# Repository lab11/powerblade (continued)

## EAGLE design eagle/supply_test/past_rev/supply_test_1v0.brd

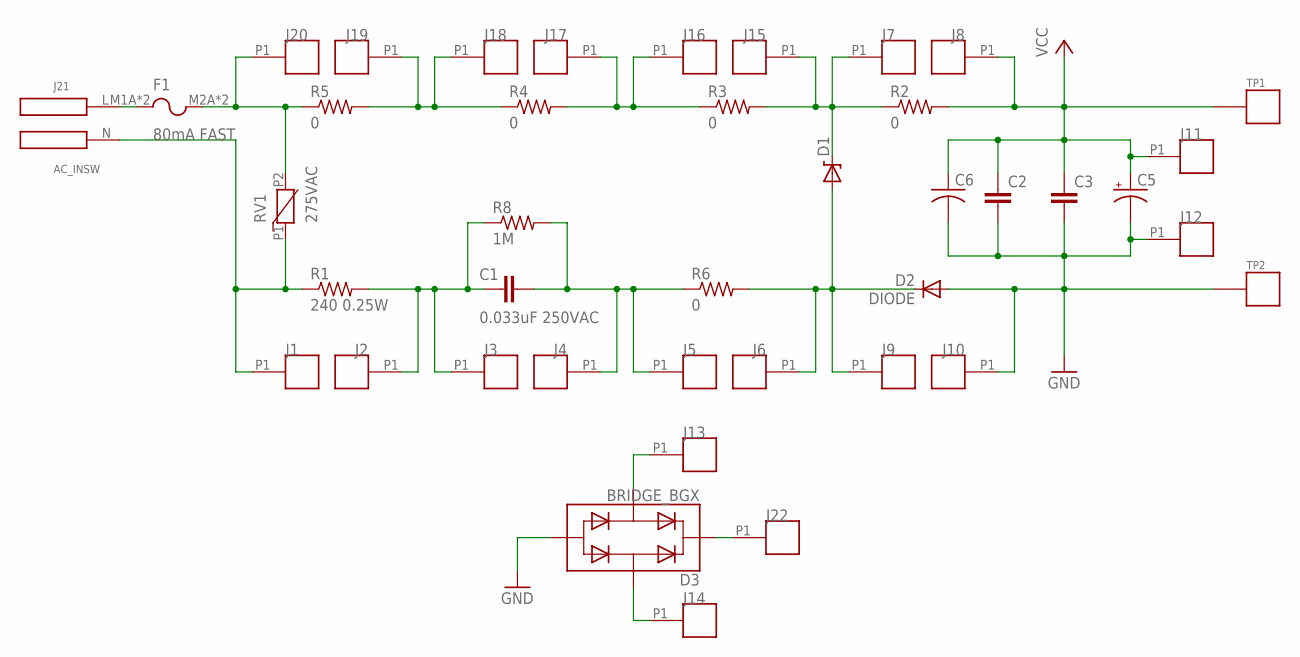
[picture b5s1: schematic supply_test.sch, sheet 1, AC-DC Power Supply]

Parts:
C1: 0.033uF 250VAC; C2220K; DIGIKEY 490-4238-1-ND
C2: C-EUC0805; C0805; DIGIKEY 445-8238-1-ND
C3: C-EUC0603; C0603; DIGIKEY 718-1672-1-ND
C5: CAP_POL1206; EIA3216; DIGIKEY NP
C6: C-USC1210; C1210; DIGIKEY 478-8408-1-ND
D1: ZENERBZT52; BZT52; DIGIKEY_2 BZT585B5V1T-7DICT-ND
D2: DIODE; BAS521
D3: BRIDGE_BGX; TO-253-4
F1: 80mA FAST; FUSE
J1, J2, J3, J4, J5, J6, J7, J8, J9, J10, J11, J12, J15, J16, J17, J18, J19, J20: SOCKET; SOCKET_1MM
J13, J14, J22: SOCKET; SOCKET_1MM; DIGIKEY ED90076-ND
J21: AC_INSW; AC_DC21; DIGIKEY_2 AE9888-ND
R1: 240 0.25W; R0603; DIGIKEY RHM240DCT-ND
R2, R3, R4, R5, R6: 0; R0603; DIGIKEY P0.0GCT-ND
R8: 1M; R0603; DIGIKEY MCT0603-1.00M-CFCT-ND
RV1: 275VAC; MOV_4032
TP1: TP_STD; TP; DIGIKEY 5000K-ND
TP2: TP_STD; TP; DIGIKEY 5001K-ND

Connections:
GND: C2.2, C3.2, C5.C (-), C6.2, D2.A, D3.P3, J10.P1, J12.P1, TP2.P$1; also elsewhere on the board
unnamed: C1.2, J2.P1, J3.P1, R1.2, R8.1
unnamed: J1.P1, J21.N, R1.1, RV1.P1
unnamed: C1.1, J4.P1, J5.P1, R6.1, R8.2
unnamed: D1.A, D2.C, J6.P1, J9.P1, R6.2
unnamed: D1.C, J7.P1, J15.P1, R2.1, R3.2
unnamed: D3.P2, J13.P1
unnamed: D3.P1, J22.P1
unnamed: D3.P4, J14.P1
unnamed: F1.M1A (P1), F1.M1B (P1), J21.L
unnamed: J16.P1, J17.P1, R3.1, R4.2
unnamed: F1.M2A (P2), F1.M2B (P2), J20.P1, R5.1, RV1.P2
unnamed: J18.P1, J19.P1, R4.1, R5.2
VCC: C2.1, C3.1, C5.A (+), C6.1, J8.P1, J11.P1, R2.2, TP1.P$1; also elsewhere on the board

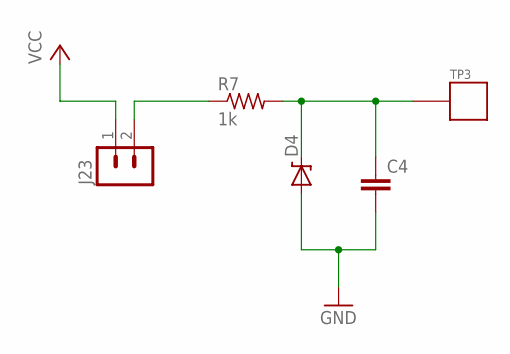
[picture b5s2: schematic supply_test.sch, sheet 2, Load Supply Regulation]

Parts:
C4: C-EUC0603; C0603; DIGIKEY 445-8028-1-ND
D4: ZENERBZT52; BZT52
J23: MA02-1STR; MA02-1; DIGIKEY 609-4434-ND
R7: 1k; R0603; DIGIKEY P1.0KGCT-ND
TP3: TP_STD; TP; DIGIKEY 5000K-ND

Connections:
GND: C4.2, D4.A; also elsewhere on the board
unnamed: J23.2, R7.1
unnamed: C4.1, D4.C, R7.2, TP3.P$1
VCC: J23.1; also elsewhere on the board

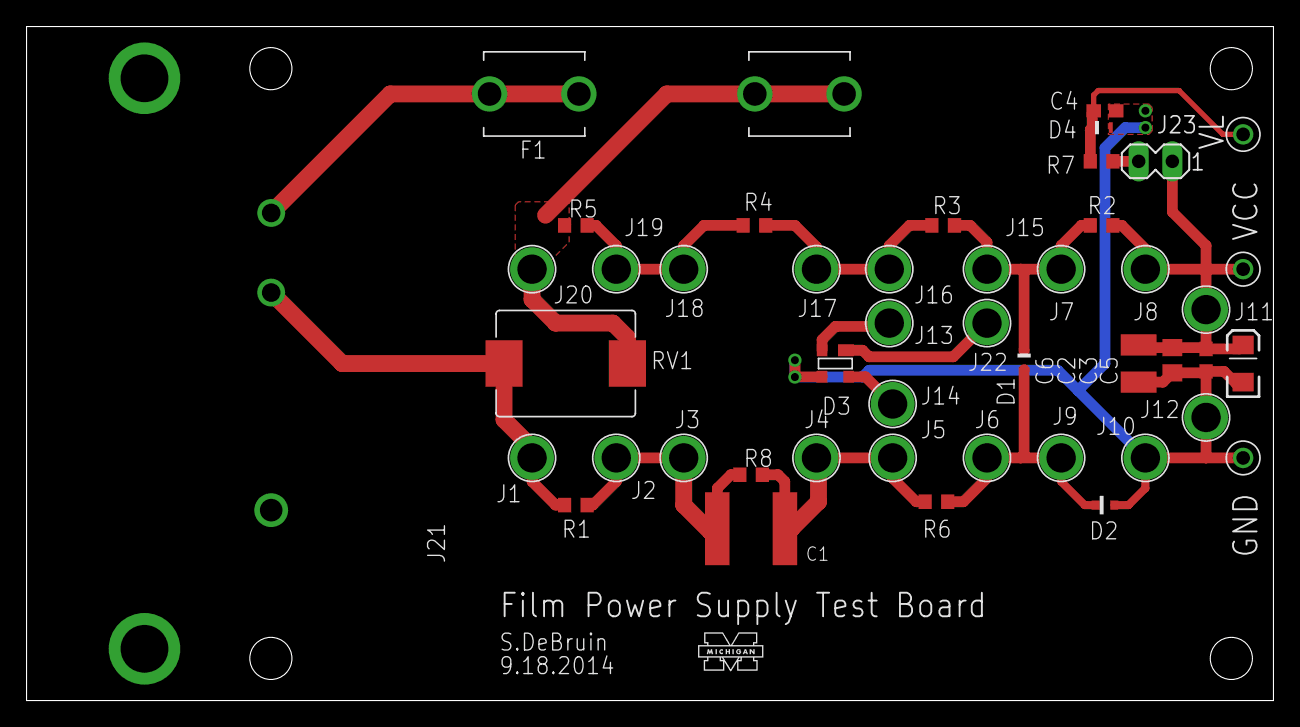
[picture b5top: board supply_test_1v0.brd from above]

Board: 2 copper layers, 94.0 x 50.8 mm, 47 parts (0 on the bottom side), 16 nets.

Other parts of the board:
U$1: UMICH

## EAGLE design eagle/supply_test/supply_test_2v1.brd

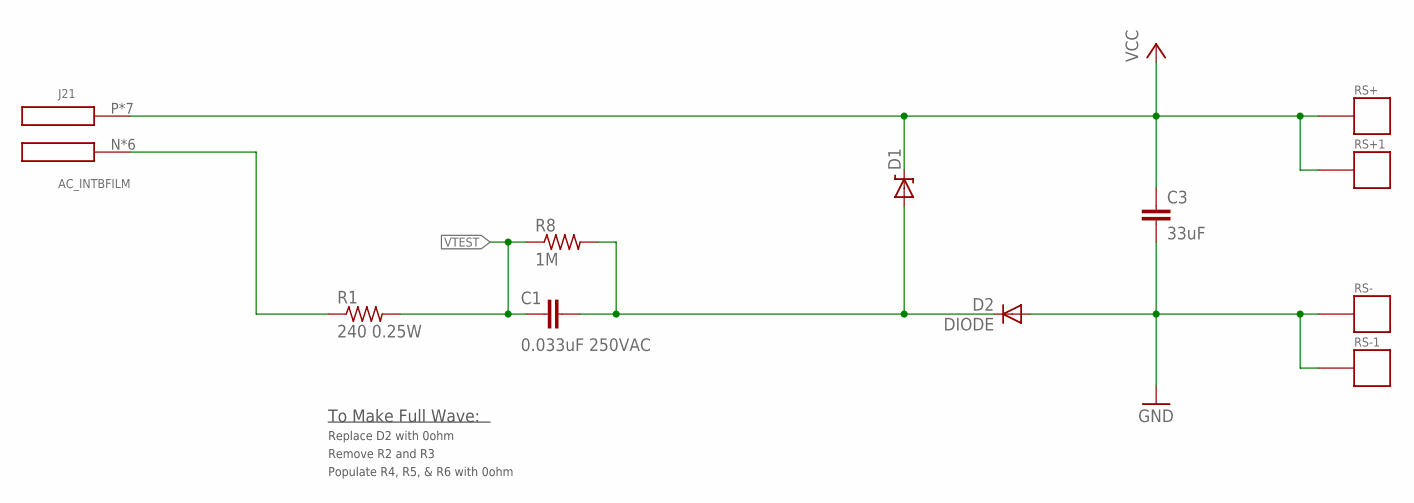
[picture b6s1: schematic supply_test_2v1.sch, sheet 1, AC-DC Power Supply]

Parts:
C1: 0.033uF 250VAC; C2220-EDGE; DIGIKEY 490-4238-1-ND
C3: 33uF; C0603; DIGIKEY 718-1672-1-ND
D1: ZENERBZT52; BZT52; DIGIKEY BZT52C10T-7DICT-ND
D2: DIODE; BAS521
J21: AC_INTBFILM; AC3_TBFILM; DIGIKEY NP
R1: 240 0.25W; R0603; DIGIKEY RHM240DCT-ND
R8: 1M; R0603; DIGIKEY MCT0603-1.00M-CFCT-ND
RS+: TP_LONG; DIGIKEY NP
RS+1: TP_SMD; DIGIKEY NP
RS-: TP_LONG; DIGIKEY NP
RS-1: TP_SMD; DIGIKEY NP

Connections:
GND: C3.2, D2.A, RS-.P$1, RS-1.P$1; also elsewhere on the board
unnamed: J21.N, J21.N1 (N), J21.N2 (N), J21.N3 (N), J21.N4 (N), J21.N5 (N), R1.1
unnamed: C1.1, D1.A, D2.C, R8.2
VCC: C3.1, D1.C, J21.P, J21.P1, J21.P2, J21.P3, J21.P4, J21.P5, J21.P6, RS+.P$1, RS+1.P$1; also elsewhere on the board
VTEST: C1.2, R1.2, R8.1; also elsewhere on the board

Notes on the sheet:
To Make Full Wave:
Replace D2 with 0ohm
Remove R2 and R3
Populate R4, R5, & R6 with 0ohm

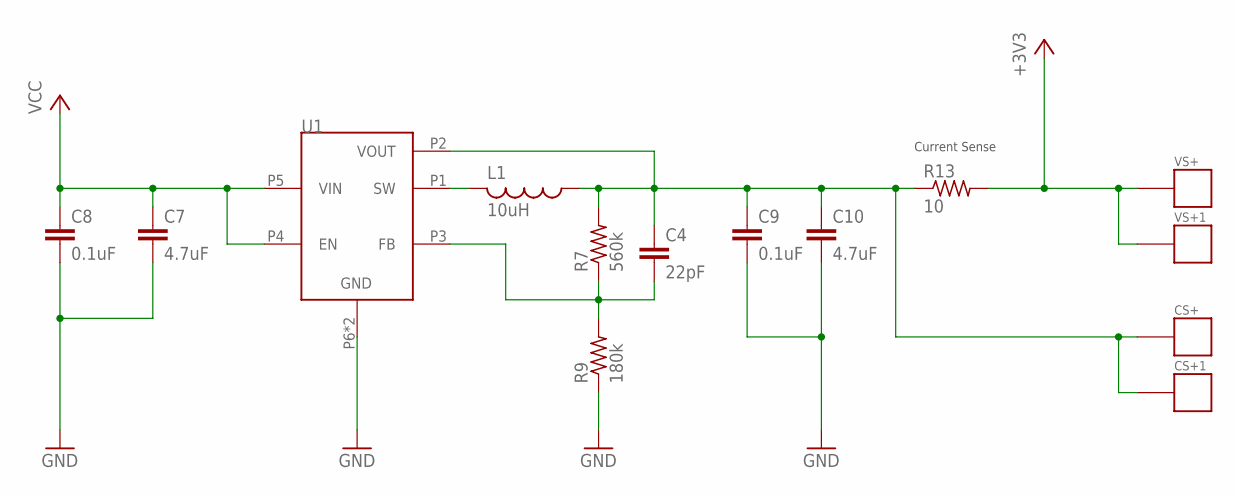
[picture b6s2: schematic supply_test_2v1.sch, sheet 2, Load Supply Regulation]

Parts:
C4: 22pF; C0402
C7: 4.7uF; C0402; DIGIKEY 587-2786-1-ND
C8, C9: 0.1uF; C0402; DIGIKEY 1276-1001-1-ND
C10: 4.7uF; C0603; DIGIKEY 587-2786-1-ND
CS+: TP_LONG; DIGIKEY NP
CS+1: TP_SMD; DIGIKEY NP
L1: 10uH; L0805; DIGIKEY 490-4990-1-ND
R7: 560k; R0402
R9: 180k; R0402
R13: 10; R0603; DIGIKEY CRT0603-BY-10R0ELFCT-ND
U1: TPS62122; WDFN-6
VS+: TP_LONG; DIGIKEY NP
VS+1: TP_SMD; DIGIKEY NP

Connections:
+3V3: R13.2, VS+.P$1, VS+1.P$1; also elsewhere on the board
GND: C7.2, C8.2, C9.2, C10.2, R9.1, U1.P6 (GND), U1.PAD (GND); also elsewhere on the board
unnamed: L1.2, U1.P1 (SW)
unnamed: C4.1, C9.1, C10.1, CS+.P$1, CS+1.P$1, L1.1, R7.2, R13.1, U1.P2 (VOUT)
unnamed: C4.2, R7.1, R9.2, U1.P3 (FB)
VCC: C7.1, C8.1, U1.P4 (EN), U1.P5 (VIN); also elsewhere on the board

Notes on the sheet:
Current Sense

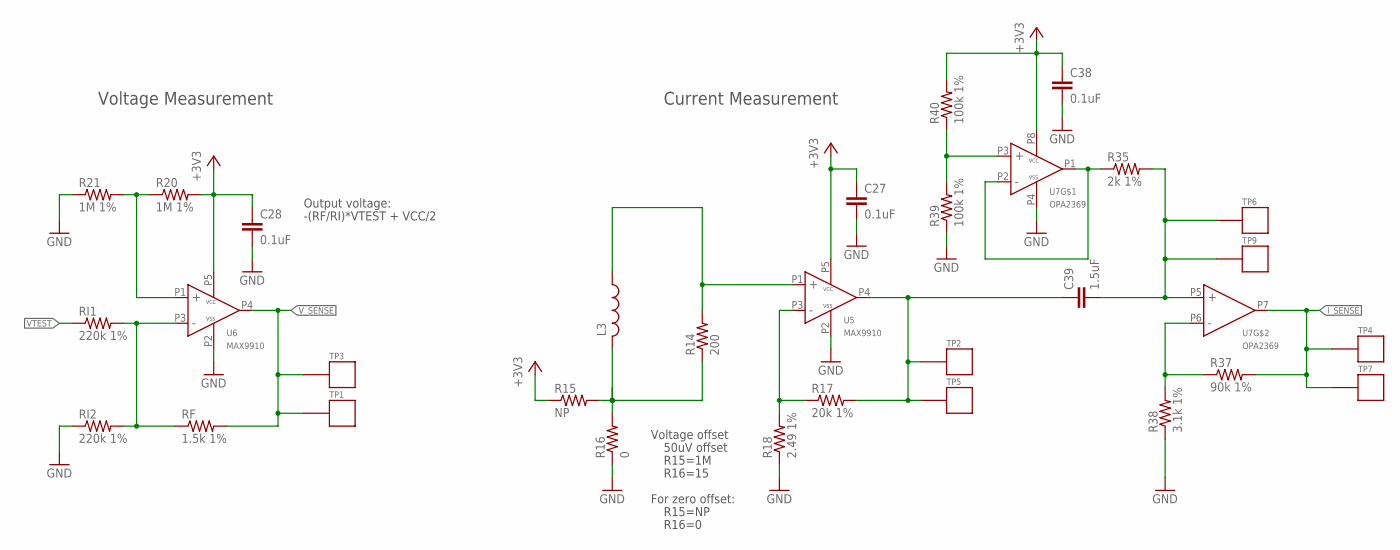
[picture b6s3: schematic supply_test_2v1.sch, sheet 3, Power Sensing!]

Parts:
C27, C28, C38: 0.1uF; C0402; DIGIKEY 445-1265-1-ND
C39: 1.5uF; C0402; DIGIKEY 445-13874-1-ND
L3: L-USL0805; L0805; DIGIKEY 732-3452-1-ND
R14: 200; R0402; DIGIKEY P200LCT-ND
R15: NP; R0402; DIGIKEY NP
R16: 0; R0402; DIGIKEY P0.0JCT-ND
R17: 20k 1%; R0402; DIGIKEY P20.0KLCT-ND
R18: 2.49 1%; R0402; DIGIKEY 541-2.49LLCT-ND
R20, R21: 1M 1%; R0402; DIGIKEY P10.0KLCT-ND
R35: 2k 1%; R0402; DIGIKEY P2.00KLCT-ND
R37: 90k 1%; R0402; DIGIKEY P90.9KLCT-ND
R38: 3.1k 1%; R0402; DIGIKEY P3.09KHCT-ND
R39, R40: 100k 1%; R0402; DIGIKEY P100KLCT-ND
RF: 1.5k 1%; R0402; DIGIKEY P1.50KLCT-ND
RI1, RI2: 220k 1%; R0402; DIGIKEY P220KLCT-ND
TP1: TP_SMD; DIGIKEY 5129K-ND
TP2, TP4, TP9: TP_LONG; DIGIKEY 5126K-ND
TP3: TP_LONG; DIGIKEY 5129K-ND
TP5, TP6, TP7: TP_SMD; DIGIKEY 5126K-ND
U5, U6: MAX9910; SC70-5
U7: OPA2369; SOT-23-8

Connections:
+3V3: C27.1, C28.1, C38.1, R15.1, R20.2, R40.2, U5.P5 (VCC), U6.P5 (VCC), U7.P8 (VCC); also elsewhere on the board
GND: C27.2, C28.2, C38.2, R16.1, R18.1, R21.1, R38.1, R39.1, RI2.1, U5.P2 (VSS), U6.P2 (VSS), U7.P4 (VSS); also elsewhere on the board
I_SENSE: R37.2, TP4.P$1, TP7.P$1, U7.P7 (OUT)
unnamed: L3.2, R14.1, R15.2, R16.2
unnamed: L3.1, R14.2, U5.P1 (IN+)
unnamed: R20.1, R21.2, U6.P1 (IN+)
unnamed: RF.1, RI1.2, RI2.2, U6.P3 (IN-)
unnamed: C39.1, R17.2, TP2.P$1, TP5.P$1, U5.P4 (OUT)
unnamed: R17.1, R18.2, U5.P3 (IN-)
unnamed: R37.1, R38.2, U7.P6 (IN-)
unnamed: C39.2, R35.2, TP6.P$1, TP9.P$1, U7.P5 (IN+)
unnamed: R35.1, U7.P1 (OUT), U7.P2 (IN-)
unnamed: R39.2, R40.1, U7.P3 (IN+)
VTEST: RI1.1; also elsewhere on the board
V_SENSE: RF.2, TP1.P$1, TP3.P$1, U6.P4 (OUT)

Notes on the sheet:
Voltage offset
50uV offset
For zero offset:
R15=NP
R16=0
Current Measurement
Voltage Measurement
Output voltage:
-(RF/RI)*VTEST + VCC/2
R15=1M
R16=15

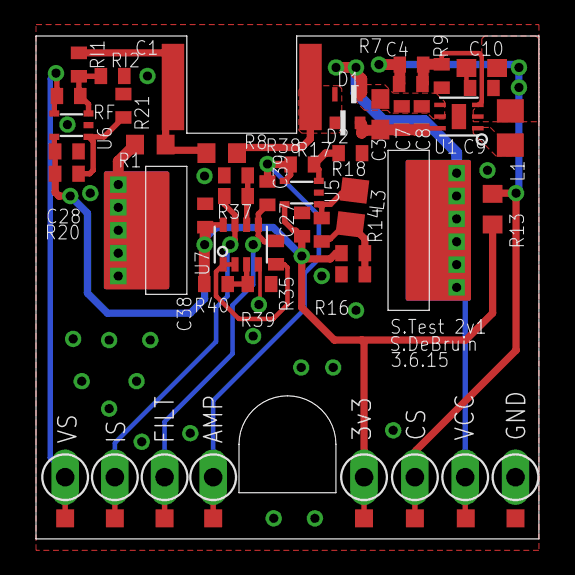
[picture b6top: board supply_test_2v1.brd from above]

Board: 2 copper layers, 27.9 x 27.9 mm, 56 parts (0 on the bottom side), 21 nets.
